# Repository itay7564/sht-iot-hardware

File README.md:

# sht-iot-hardware
Hardware designs for sht-iot devices. Mainly ESP8266 boards.

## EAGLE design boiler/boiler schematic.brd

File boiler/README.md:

Boiler controller board with an ESP8266 module, which connects to the sht-iot server to control the Boiler.

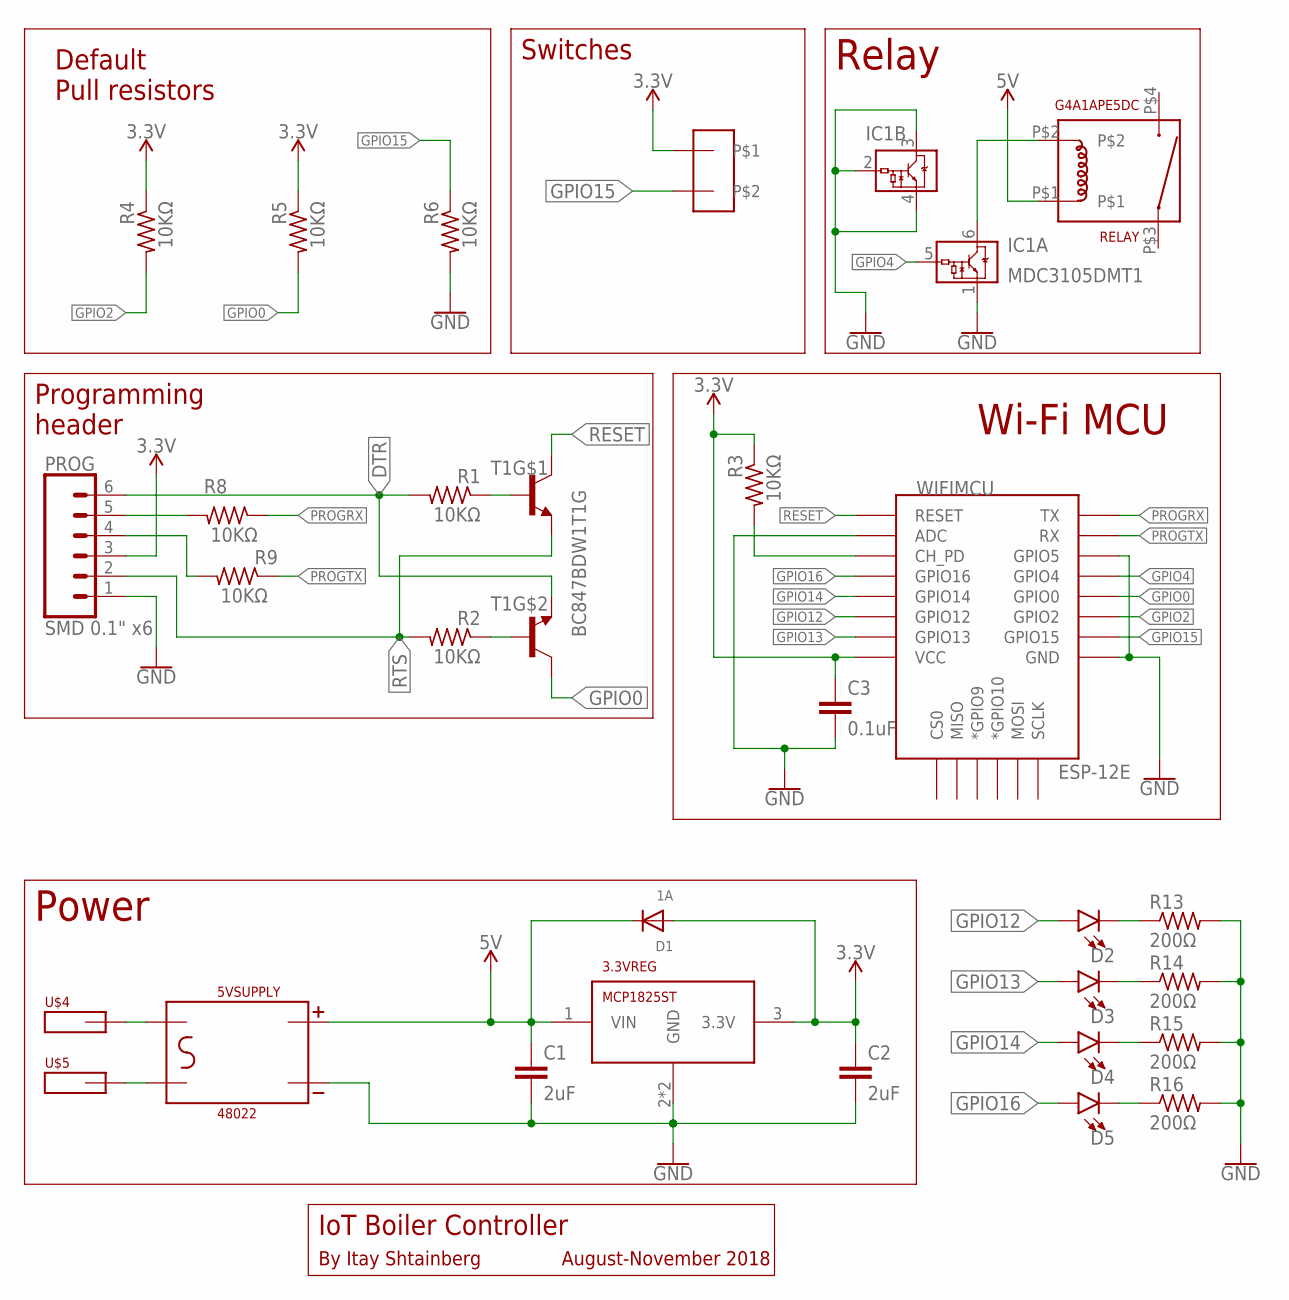
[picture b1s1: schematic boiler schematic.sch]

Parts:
3.3VREG: MCP1825ST; SOT223
5VSUPPLY: 48022
C1, C2: 2uF; C0805
C3: 0.1uF; C0805
D1: 1A; SOD-123
D2, D3, D4, D5: LED1206; LED-1206
IC1: MDC3105DMT1; SC-74
PROG: SMD 0.1" x6; 1X06-SMD-FEMALE
R1, R2, R3, R4, R5, R6, R8, R9: 10KΩ; R0805
R13, R14, R15, R16: 200Ω; R1206
RELAY: G4A1APE5DC; G4A-1A-E
T1: BC847BDW1T1G; SC70-6
U$1: JST2PIN
U$4, U$5: QUICKDISCONNECT2
WIFIMCU: ESP-12E; ESP12E-SMD

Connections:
3.3V: 3.3VREG.3 (3.3V), C2.1, C3.1, D1.A, PROG.3, R3.1, R4.1, R5.1, U$1.P$1, WIFIMCU.VCC
5V: 3.3VREG.1 (VIN), 5VSUPPLY.+5V, C1.1, D1.C, RELAY.P$1
DTR: PROG.6, R1.2, T1.4 (E)
GND: 3.3VREG.2 (GND), 3.3VREG.4 (GND), 5VSUPPLY.-, C1.2, C2.2, C3.2, IC1.1 (GND), IC1.2 (VIN), IC1.3 (VOUT), IC1.4 (GND), PROG.1, R6.2, R13.2, R14.2, R15.2, R16.2, WIFIMCU.ADC, WIFIMCU.GND, WIFIMCU.GPIO5
GPIO0: R5.2, T1.3 (C), WIFIMCU.GPIO0
GPIO2: R4.2, WIFIMCU.GPIO2
GPIO4: IC1.5 (VIN), WIFIMCU.GPIO4
GPIO12: D2.A, WIFIMCU.GPIO12
GPIO13: D3.A, WIFIMCU.GPIO13
GPIO14: D4.A, WIFIMCU.GPIO14
GPIO15: R6.1, U$1.P$2, WIFIMCU.GPIO15
GPIO16: D5.A, WIFIMCU.GPIO16
unnamed: 5VSUPPLY.AC1, U$4.P$1, U$4.P$2, U$4.P$3, U$4.P$4
unnamed: 5VSUPPLY.AC2, U$5.P$1, U$5.P$2, U$5.P$3, U$5.P$4
unnamed: D2.C, R13.1
unnamed: IC1.6 (VOUT), RELAY.P$2
unnamed: R1.1, T1.2 (B)
unnamed: PROG.4, R9.2
unnamed: R2.1, T1.5 (B)
unnamed: PROG.5, R8.2
unnamed: D3.C, R14.1
unnamed: D4.C, R15.1
unnamed: D5.C, R16.1
unnamed: R3.2, WIFIMCU.CH_PD
PROGRX: R8.1, WIFIMCU.TXD0 (TX)
PROGTX: R9.1, WIFIMCU.RXD0 (RX)
RESET: T1.6 (C), WIFIMCU.RESET
RTS: PROG.2, R2.2, T1.1 (E)

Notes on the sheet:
Power
Relay
Wi-Fi MCU
Programming header
Default Pull resistors
Switches
IoT Boiler Controller
By Itay Shtainberg
August-November 2018

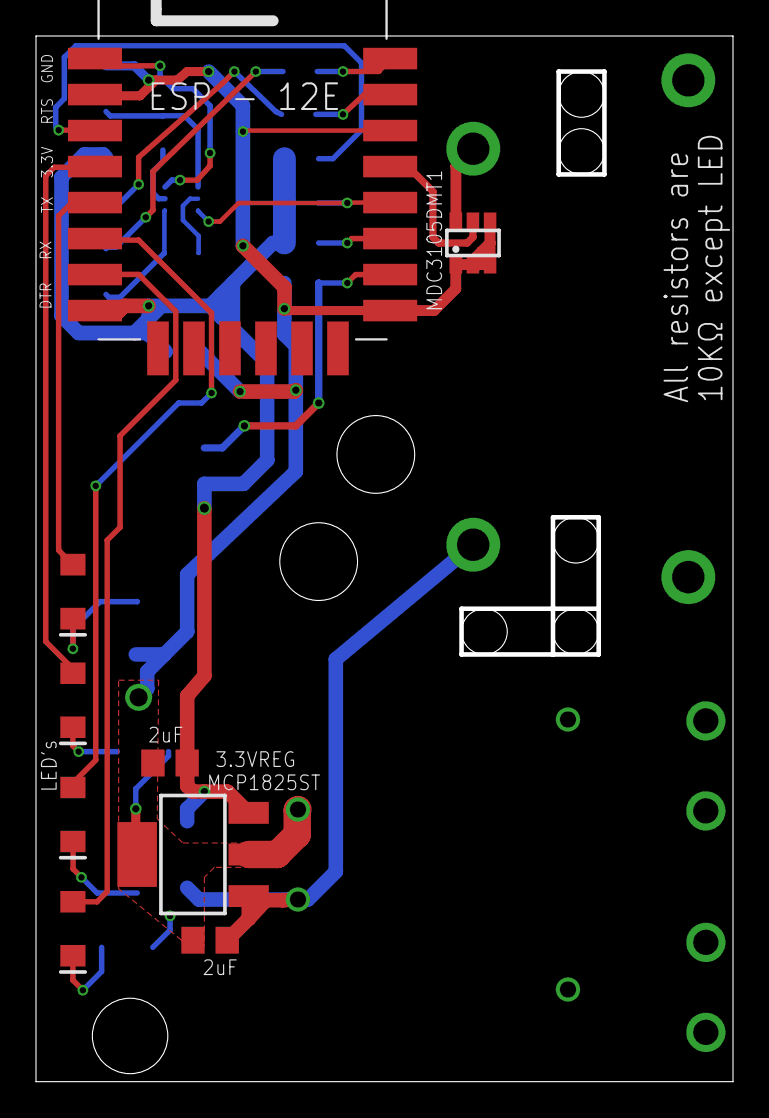
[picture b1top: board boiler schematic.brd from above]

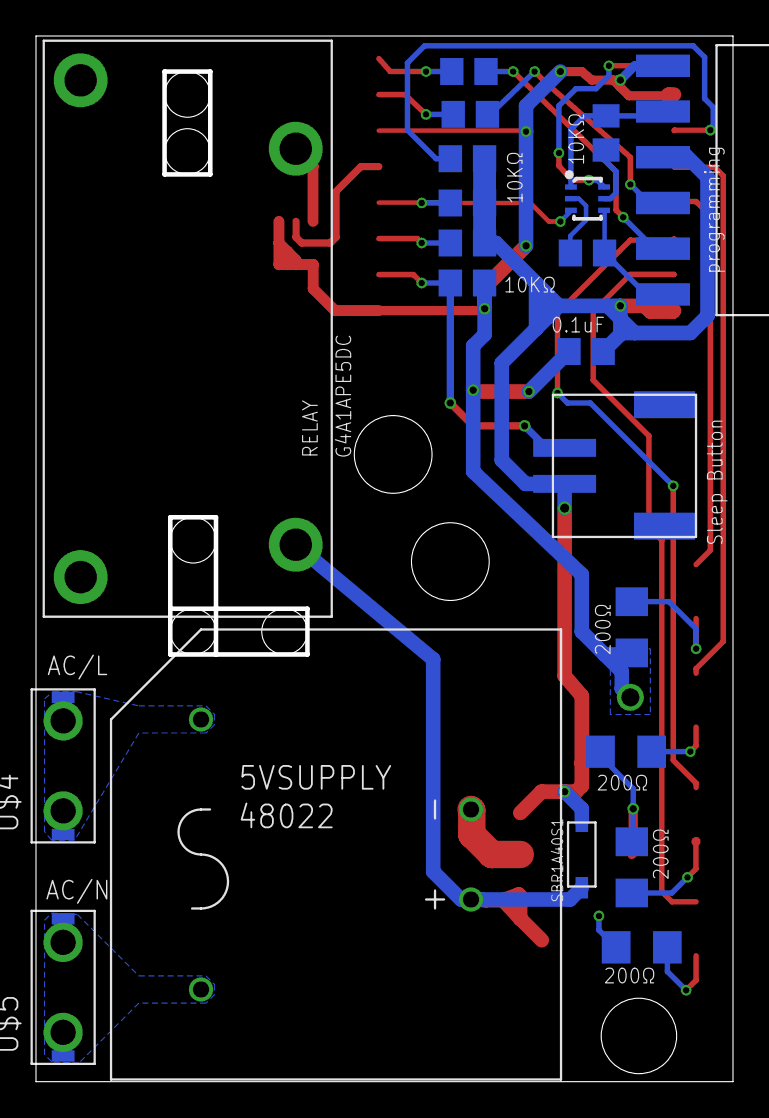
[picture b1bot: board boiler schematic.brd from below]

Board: 2 copper layers, 38.5 x 57.8 mm, 30 parts (21 on the bottom side), 28 nets.

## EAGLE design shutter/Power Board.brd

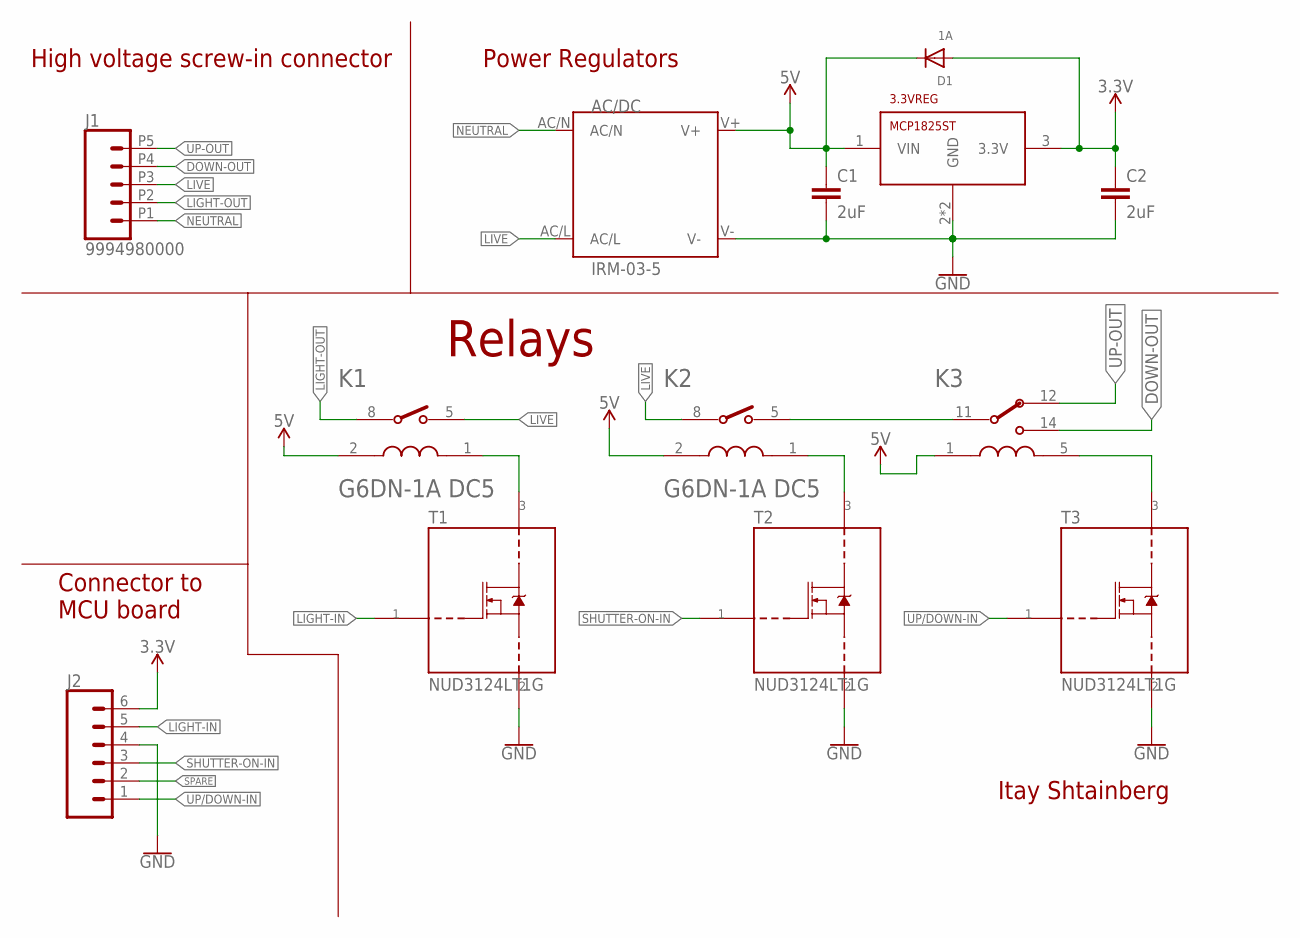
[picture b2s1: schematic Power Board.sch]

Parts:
3.3VREG: MCP1825ST; SOT223
AC/DC: IRM-03-5; IRM_03
C1, C2: 2uF; C0805
D1: 1A; SOD-123
J1: 9994980000
J2: CONN_06FEMALE_LOCK; 1X06_FEMALE_LOCK.010
K1, K2: G6DN-1A-L DC5; OMRON_G6DN-1A_DC5_0
K3: PE014005; RELAY5-PE_CO
T1, T2, T3: NUD3124LT1G; SOT23

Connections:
3.3V: 3.3VREG.3 (3.3V), C2.1, D1.A, J2.6
5V: 3.3VREG.1 (VIN), AC/DC.V+, C1.1, D1.C, K1.2, K2.2, K3.1 (COIL1)
DOWN-OUT: J1.P4 (4), K3.14 (NO)
GND: 3.3VREG.2 (GND), 3.3VREG.4 (GND), AC/DC.V-, C1.2, C2.2, J2.4, T1.2, T2.2, T3.2
LIGHT-IN: J2.5, T1.1
LIGHT-OUT: J1.P2 (2), K1.8
LIVE: AC/DC.AC/L, J1.P3 (3), K1.5, K2.8
unnamed: K2.5, K3.11
unnamed: K1.1, T1.3
unnamed: K3.5 (COIL2), T3.3
unnamed: K2.1, T2.3
NEUTRAL: AC/DC.AC/N, J1.P1 (1)
SHUTTER-ON-IN: J2.3, T2.1
SPARE: J2.2
UP-OUT: J1.P5 (5), K3.12 (NC)
UP/DOWN-IN: J2.1, T3.1

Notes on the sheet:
High voltage screw-in connector
Power Regulators
Relays
Connector to MCU board

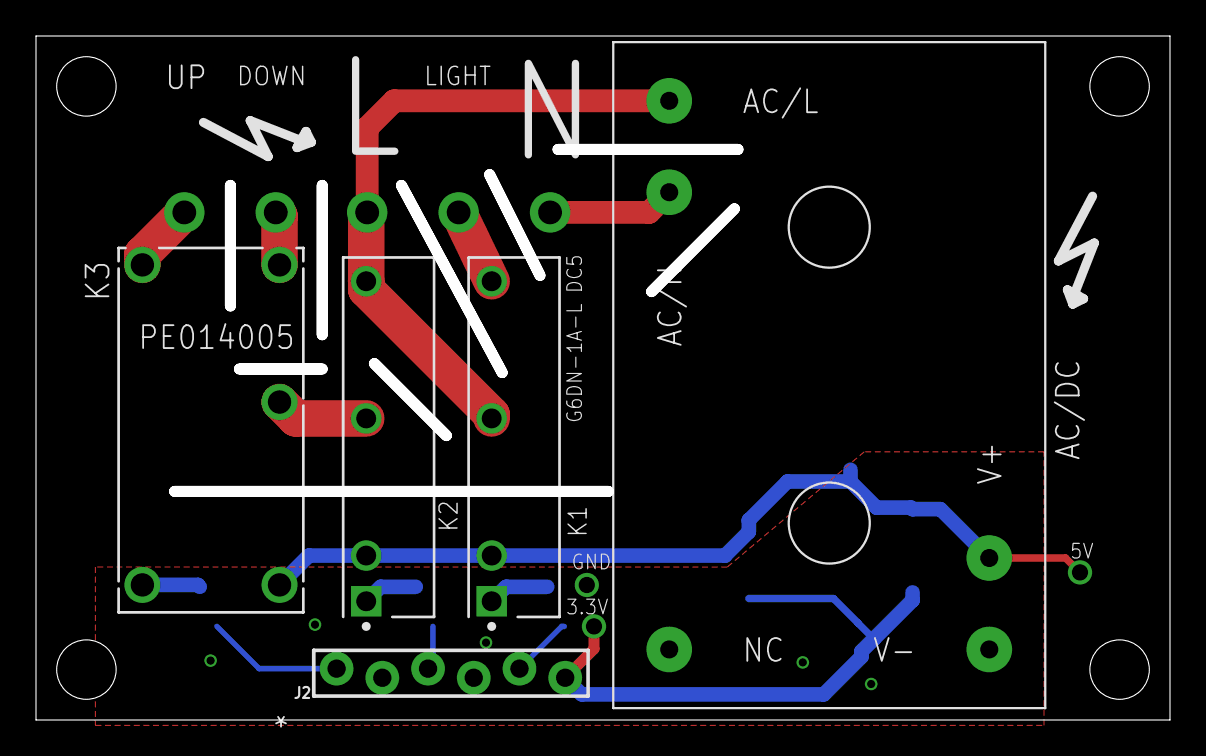
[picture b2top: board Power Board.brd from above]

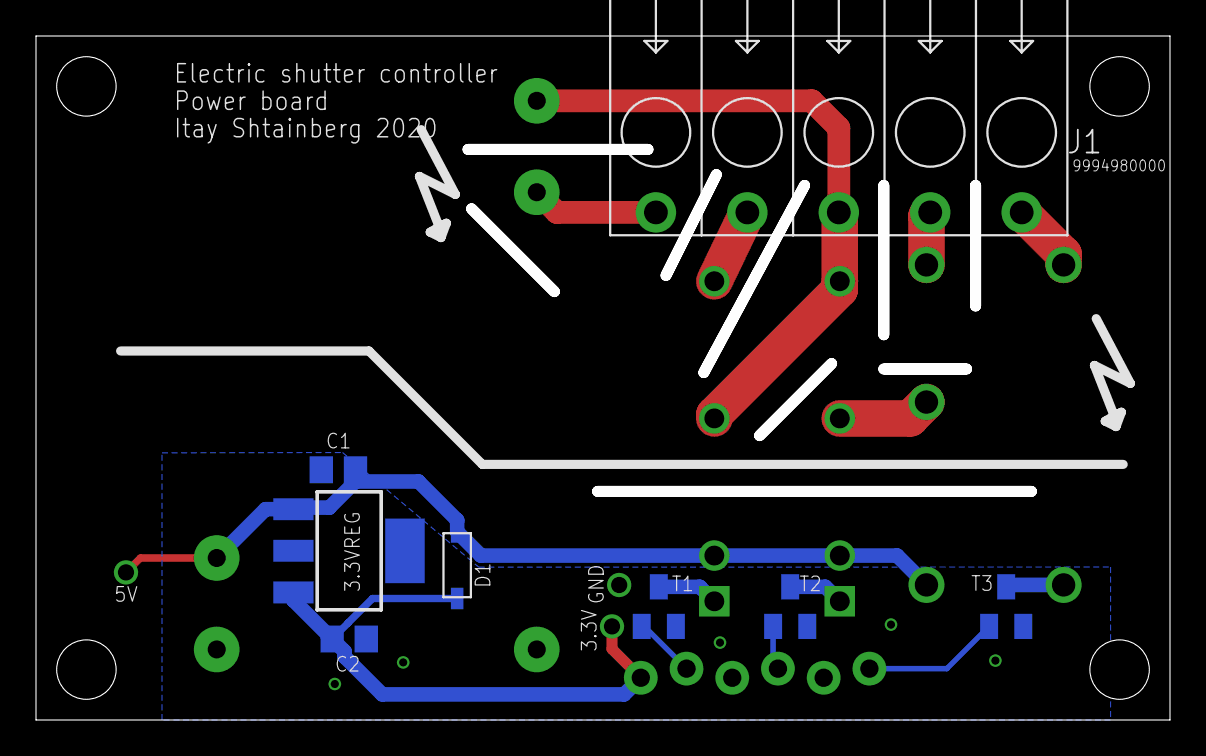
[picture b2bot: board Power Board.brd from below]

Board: 2 copper layers, 62.4 x 37.4 mm, 13 parts (8 on the bottom side), 15 nets.

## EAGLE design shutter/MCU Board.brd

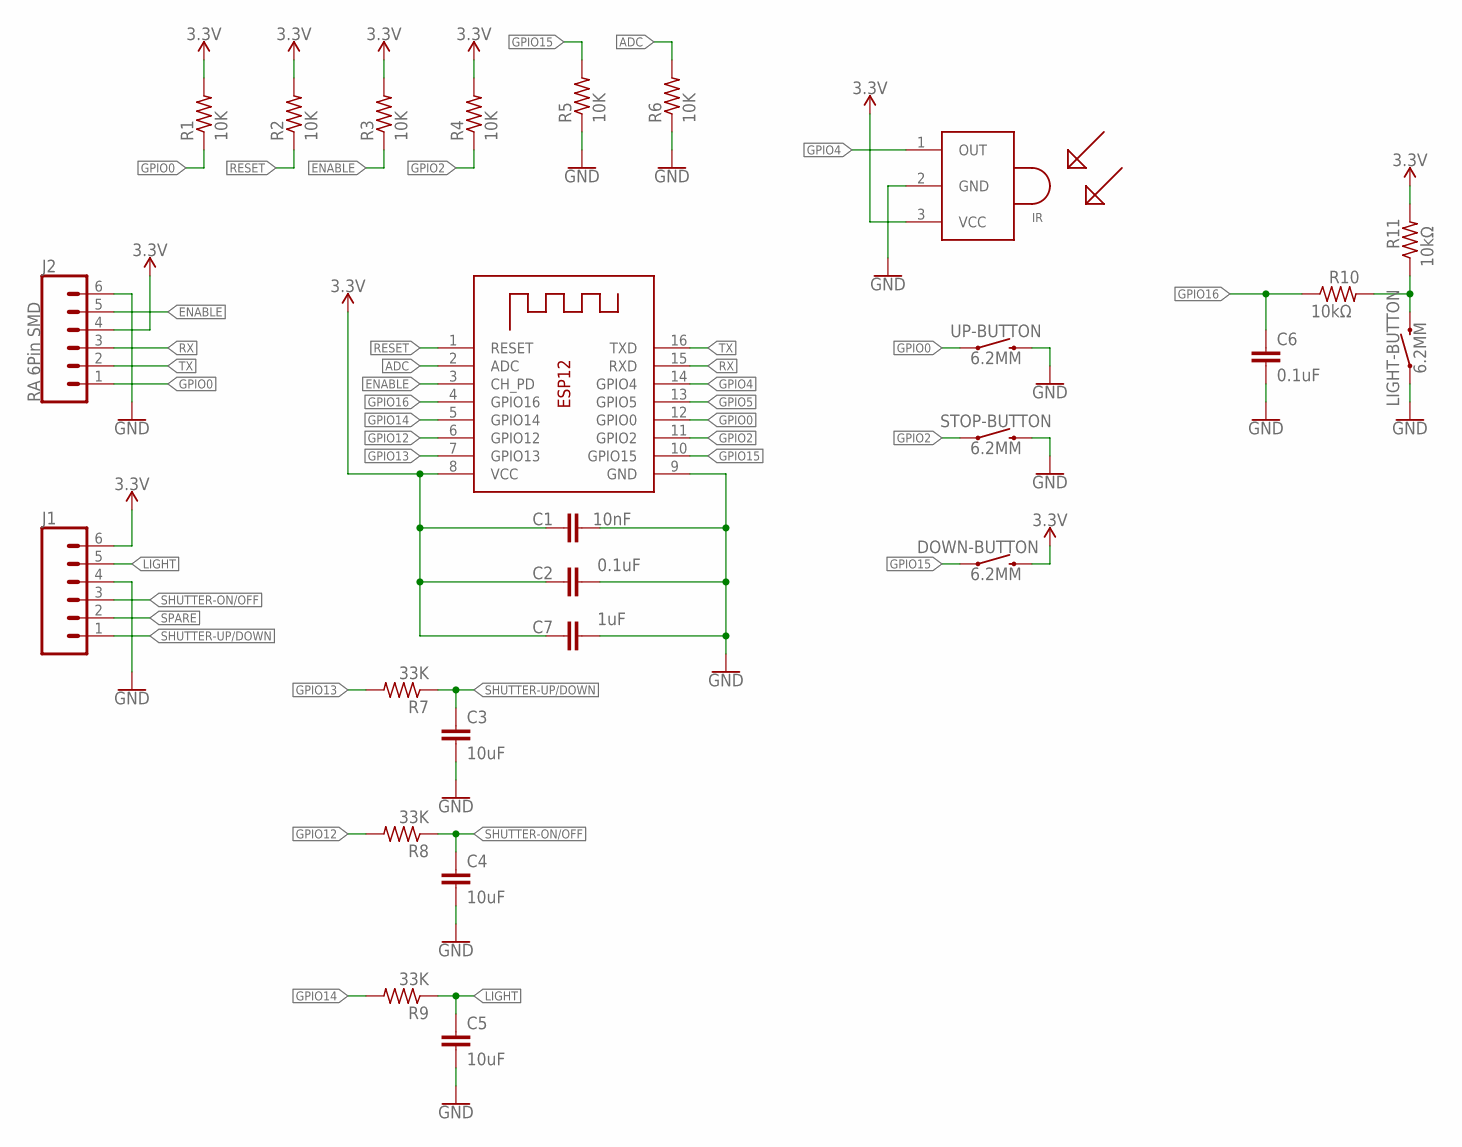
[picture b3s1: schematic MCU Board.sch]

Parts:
C1: 10nF; C0805
C2, C6: 0.1uF; C0805
C3, C4, C5: 10uF; C0805
C7: 1uF; C0805
DOWN-BUTTON: 6.2MM; TACTILE_SWITCH_SMD_6.2MM_TALL
IR: TSOP382; TSOP382**-VERTICAL
J1: CONN_06LOCK; 1X06_LOCK
J2: RA 6Pin SMD; 1X06-SMD_RA_MALE
LIGHT-BUTTON: 6.2MM; TACTILE_SWITCH_SMD_6.2MM_TALL
R1, R2, R3, R4, R5, R6: 10K; R0805
R7, R8, R9: 33K; R0805
R10, R11: 10kΩ; R0805
STOP-BUTTON: 6.2MM; TACTILE_SWITCH_SMD_6.2MM_TALL
UP-BUTTON: 6.2MM; TACTILE_SWITCH_SMD_6.2MM_TALL
X1: ESP-12

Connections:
3.3V: C1.1, C2.1, C7.1, DOWN-BUTTON.B2 (2), IR.3 (VCC), J1.6, J2.4, R1.2, R2.2, R3.2, R4.2, R11.2, X1.8 (VCC)
ADC: R6.2, X1.2 (ADC)
ENABLE: J2.5, R3.1, X1.3 (CH_PD)
GND: C1.2, C2.2, C3.2, C4.2, C5.2, C6.2, C7.2, IR.2 (GND), J1.4, J2.6, LIGHT-BUTTON.A2 (1), R5.1, R6.1, STOP-BUTTON.B2 (2), UP-BUTTON.B2 (2), X1.9 (GND)
GPIO0: J2.1, R1.1, UP-BUTTON.A2 (1), X1.12 (GPIO0)
GPIO2: R4.1, STOP-BUTTON.A2 (1), X1.11 (GPIO2)
GPIO4: IR.1 (OUT), X1.14 (GPIO4)
GPIO5: X1.13 (GPIO5)
GPIO12: R8.2, X1.6 (GPIO12)
GPIO13: R7.2, X1.7 (GPIO13)
GPIO14: R9.2, X1.5 (GPIO14)
GPIO15: DOWN-BUTTON.A2 (1), R5.2, X1.10 (GPIO15)
GPIO16: C6.1, R10.1, X1.4 (GPIO16)
LIGHT: C5.1, J1.5, R9.1
unnamed: LIGHT-BUTTON.B2 (2), R10.2, R11.1
RESET: R2.1, X1.1 (RESET)
RX: J2.3, X1.15 (RXD)
SHUTTER-ON/OFF: C4.1, J1.3, R8.1
SHUTTER-UP/DOWN: C3.1, J1.1, R7.1
SPARE: J1.2
TX: J2.2, X1.16 (TXD)

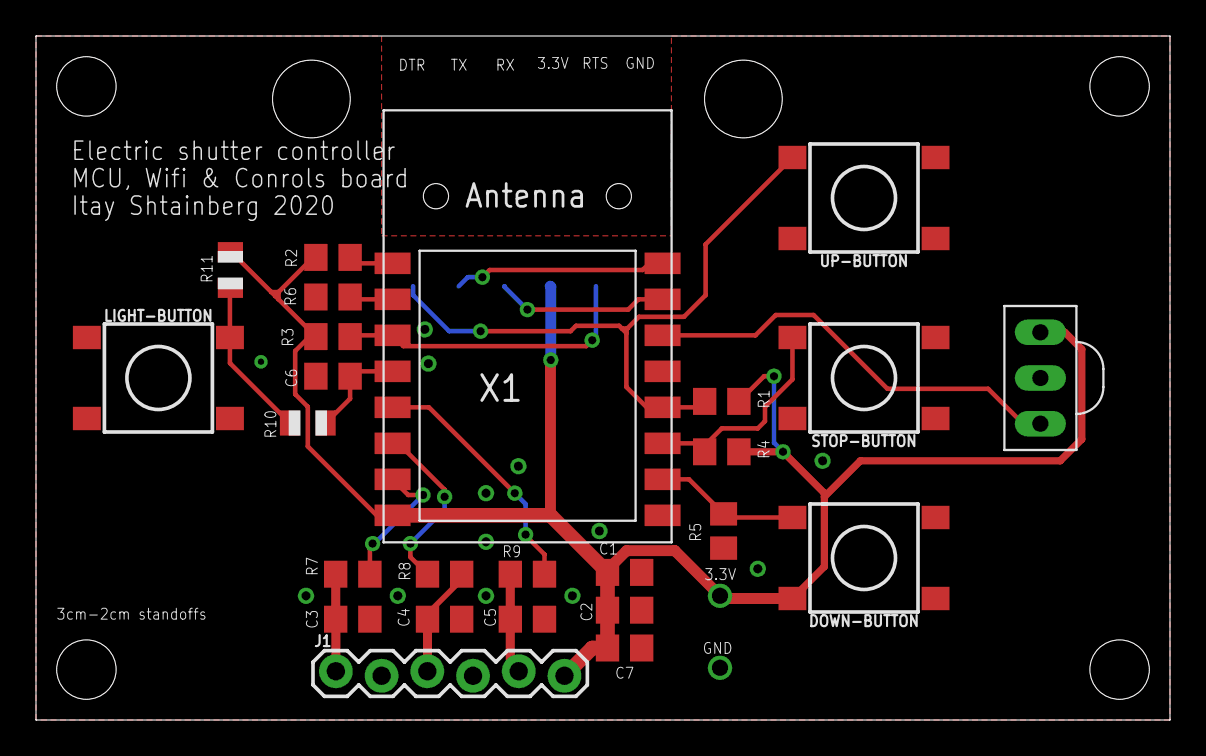
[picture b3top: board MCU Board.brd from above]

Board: 2 copper layers, 63.0 x 38.0 mm, 26 parts (1 on the bottom side), 19 nets.

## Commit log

2021-02-15 Added boiler and shutter boards

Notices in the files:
parts and their libraries:
SparkFun-Connectors: Licensing: Creative Commons ShareAlike 4.0 International - https://creativecommons.org/licenses/by-sa/4.0
COPYRIGHT: Copyright (C) 2016 Accelerated Designs. All rights reserved
